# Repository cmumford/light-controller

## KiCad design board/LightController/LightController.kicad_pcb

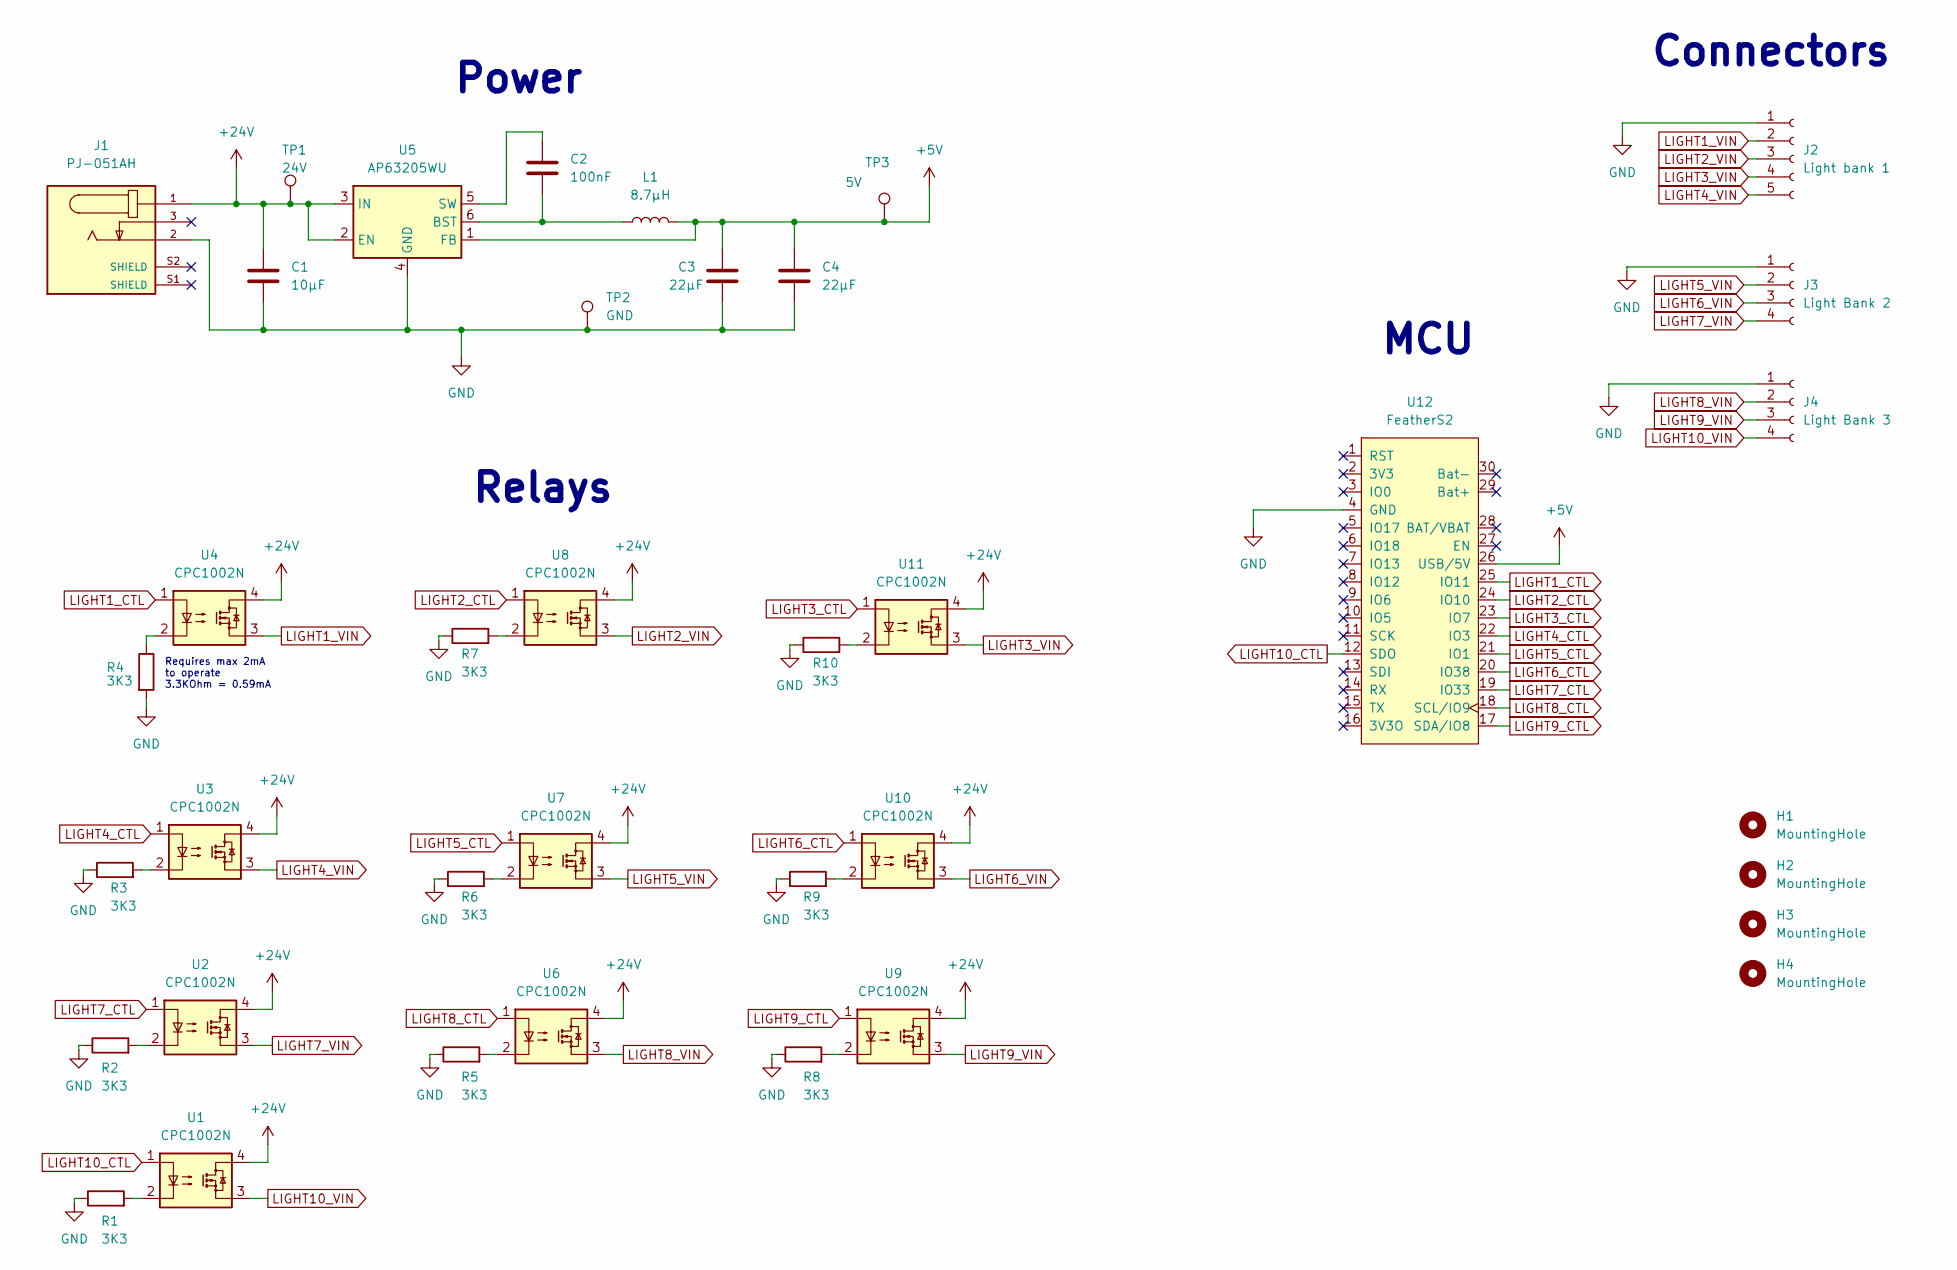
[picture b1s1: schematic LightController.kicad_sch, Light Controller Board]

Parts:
C1: 10µF; C_1206_3216Metric
C2: 100nF; C_0805_2012Metric
C3, C4: 22µF; C_1206_3216Metric
H1, H2, H3, H4: MountingHole; MountingHole_2mm
J1: PJ-051AH; PARTREV 1.03
J2: Light bank 1; PinHeader_1x05_P2.54mm_Vertical
J3: Light Bank 2; PinHeader_1x04_P2.54mm_Vertical
J4: Light Bank 3; PinHeader_1x04_P2.54mm_Vertical
L1: 8.7µH; L_0805_2012Metric
R1, R2, R3, R4, R5, R6, R7, R8, R9, R10: 3K3; R_0805_2012Metric
TP1: 24V; TestPoint_Pad_D4.0mm
TP2: GND; TestPoint_Loop_D2.54mm_Drill1.5mm_Beaded
TP3: 5V; TestPoint_Pad_D4.0mm
U1, U2, U3, U4, U6, U7, U8, U9, U10, U11: CPC1002N; SOP-4_3.8x4.1mm_P2.54mm
U5: AP63205WU; TSOT-23-6
U12: FeatherS2

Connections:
+5V: C3.1, C4.1, L1.2, TP3.1, U5.1 (FB), U12.26 (USB/5V)
+24V: C1.1, J1.1, TP1.1, U1.4, U2.4, U3.4, U4.4, U5.2 (EN), U5.3 (IN), U6.4, U7.4, U8.4, U9.4, U10.4, U11.4
GND: C1.2, C3.2, C4.2, J1.2, J2.1, J3.1, J4.1, R1.1, R2.1, R3.1, R4.2, R5.1, R6.1, R7.1, R8.1, R9.1, R10.1, TP2.1, U5.4 (GND), U12.4 (GND)
LIGHT1_CTL: U4.1, U12.25 (IO11)
LIGHT1_VIN: J2.2, U4.3
LIGHT2_CTL: U8.1, U12.24 (IO10)
LIGHT2_VIN: J2.3, U8.3
LIGHT3_CTL: U11.1, U12.23 (IO7)
LIGHT3_VIN: J2.4, U11.3
LIGHT4_CTL: U3.1, U12.22 (IO3)
LIGHT4_VIN: J2.5, U3.3
LIGHT5_CTL: U7.1, U12.21 (IO1)
LIGHT5_VIN: J3.2, U7.3
LIGHT6_CTL: U10.1, U12.20 (IO38)
LIGHT6_VIN: J3.3, U10.3
LIGHT7_CTL: U2.1, U12.19 (IO33)
LIGHT7_VIN: J3.4, U2.3
LIGHT8_CTL: U6.1, U12.18 (SCL/IO9)
LIGHT8_VIN: J4.2, U6.3
LIGHT9_CTL: U9.1, U12.17 (SDA/IO8)
LIGHT9_VIN: J4.3, U9.3
LIGHT10_CTL: U1.1, U12.12 (SDO)
LIGHT10_VIN: J4.4, U1.3
unnamed: C2.1, U5.5 (SW)
unnamed: C2.2, L1.1, U5.6 (BST)
unnamed: R1.2, U1.2
unnamed: R2.2, U2.2
unnamed: R3.2, U3.2
unnamed: R4.1, U4.2
unnamed: R5.2, U6.2
unnamed: R6.2, U7.2
unnamed: R7.2, U8.2
unnamed: R8.2, U9.2
unnamed: R9.2, U10.2
unnamed: R10.2, U11.2

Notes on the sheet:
MCU
Requires max 2mA to operate 3.3KOhm = 0.59mA
Connectors
Power
Relays

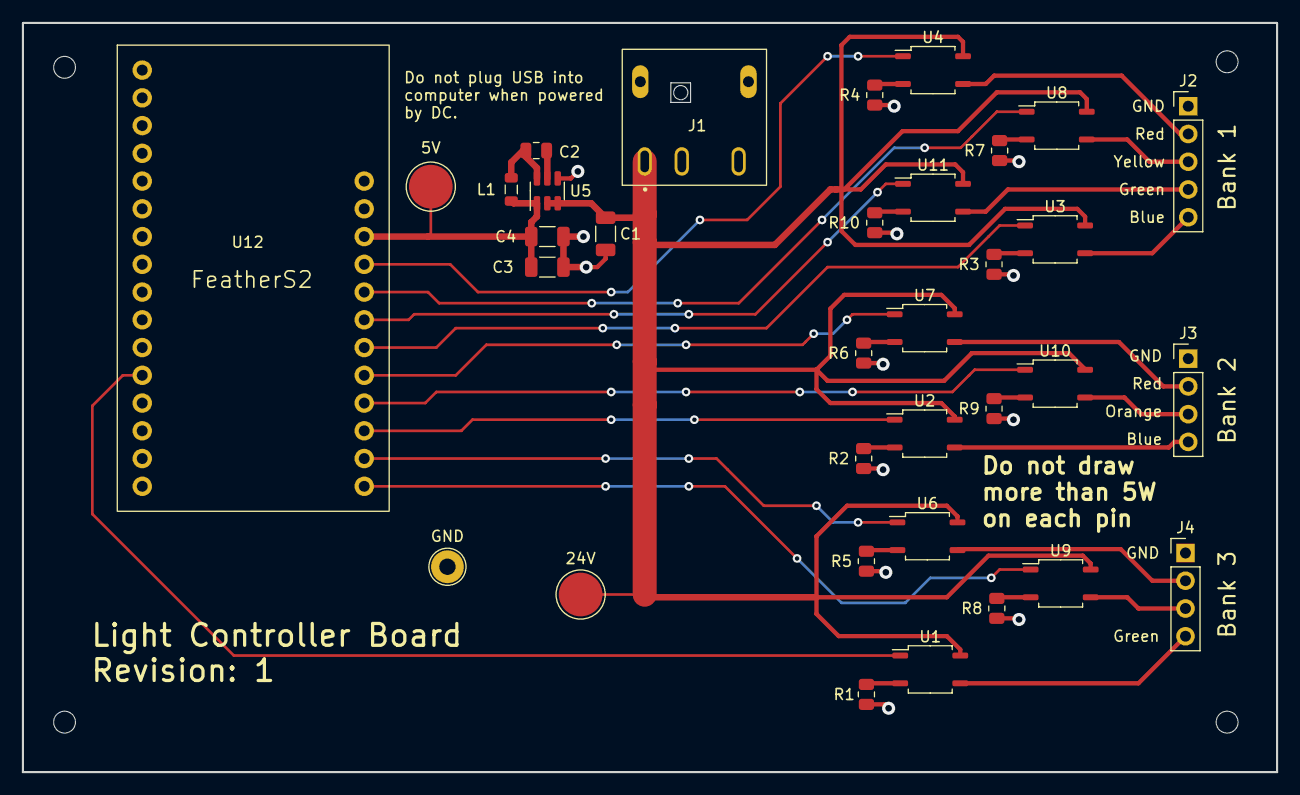
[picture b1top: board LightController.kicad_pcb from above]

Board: 2 copper layers, 114.8 x 68.6 mm, 38 parts (0 on the bottom side), 35 nets.

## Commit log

2022-08-31 Initial commit.
2022-08-31 Add .gitignore.
2022-09-01 Add mounting holes.
2022-09-01 Increase trace width and relay input resistor.
2022-09-01 Using PJ-051AH barrel DC power jack.
2022-09-02 All 10 relays.
2022-09-02 Add test points.
2022-09-02 Added second parallel bypass cap.
2022-09-03 fixed resistor label orientations.
2022-09-03 labels bold → normal.
2022-09-03 Increased caps to 1206.
2022-09-03 Increased inductor size to 1206.
2022-09-03 Set gerber output dir.
2022-11-15 Add BLE and cycle_neopixel variable.
2022-11-15 Feather S2 flash Makefile.
2022-11-15 Fixed pin 5/6 swap design issue.
2022-11-15 FeatherS3 flash make changes.
2022-11-15 App.
    Mostly a copy of the default `code.py` that comes with the
    FeatherS3.
2022-11-15 Fix pin assignments and remove BLE
2022-11-15 Cleanup app code.
2022-11-15 Changed Inductor value to 8.2µH.
    Matches the component ordered as 8.7µH is an uncommon value.
2022-11-15 Ignoring .DS_Store.
